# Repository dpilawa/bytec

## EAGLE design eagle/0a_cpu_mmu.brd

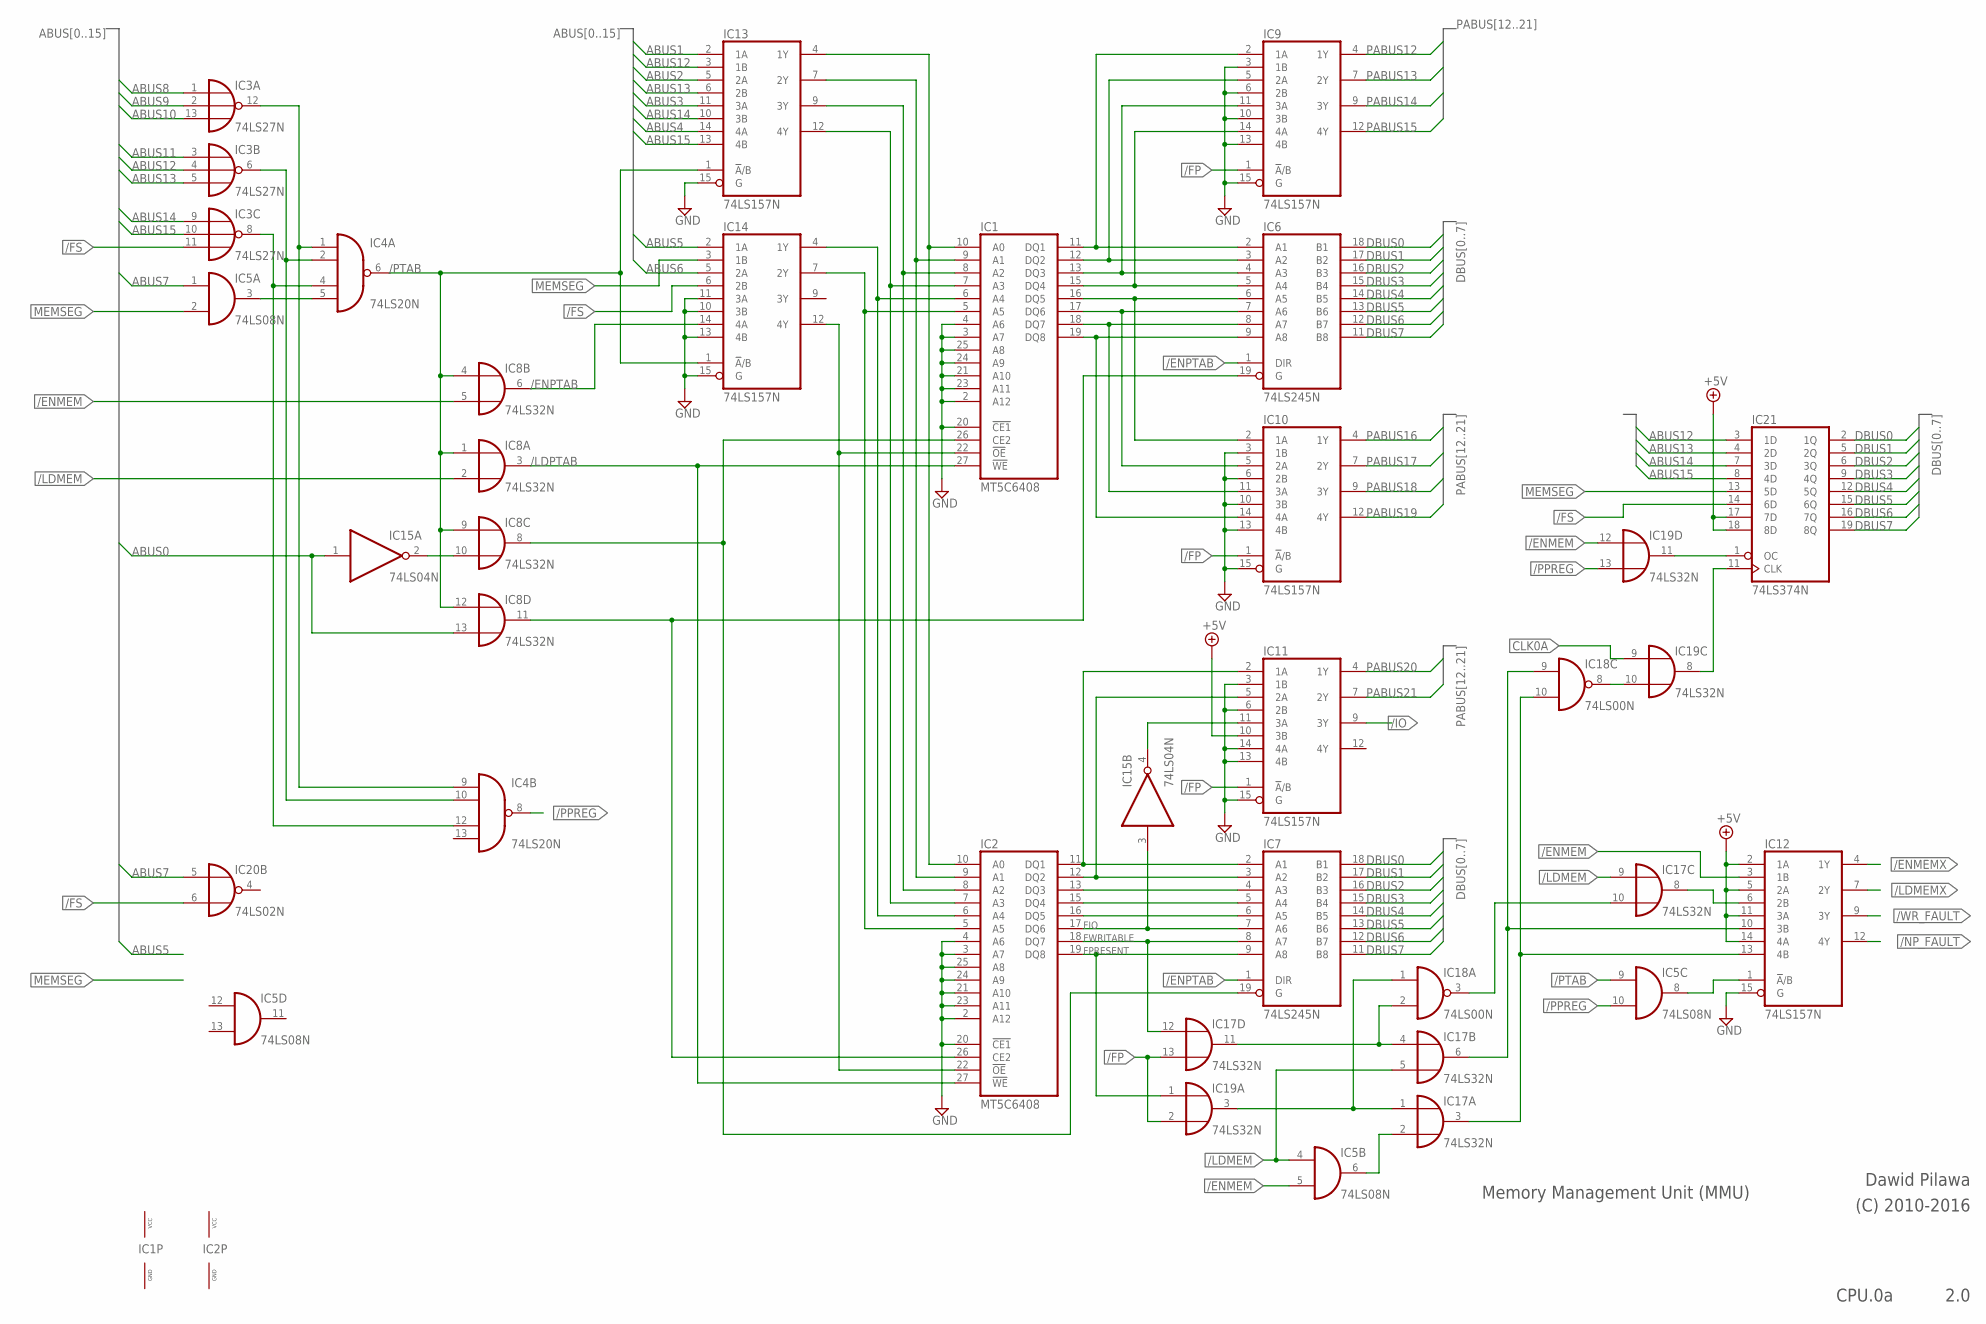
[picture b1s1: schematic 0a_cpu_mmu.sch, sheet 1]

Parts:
IC1, IC2: MT5C6408; DIL28-3
IC3: 74LS27N; DIL14
IC4: 74LS20N; DIL14
IC5: 74LS08N; DIL14
IC6, IC7: 74LS245N; DIL20
IC8, IC17, IC19: 74LS32N; DIL14
IC9, IC10, IC11, IC12, IC13, IC14: 74LS157N; DIL16
IC15: 74LS04N; DIL14
IC18: 74LS00N; DIL14
IC20: 74LS02N; DIL14
IC21: 74LS374N; DIL20

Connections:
+5V: IC11.10 (3B), IC12.2 (1A), IC12.5 (2A), IC12.11 (3A), IC12.14 (4A), IC21.17 (7D), IC21.18 (8D); also elsewhere on the board
/ENMEM: IC5.5 (I1), IC8.5 (I1), IC12.3 (1B), IC19.12 (I0); also elsewhere on the board
/ENMEMX: IC12.4 (1Y)
/ENPTAB: IC6.1 (DIR), IC7.1 (DIR), IC8.6 (O), IC14.14 (4A)
/FP: IC9.1 (!A!/B), IC10.1 (!A!/B), IC11.1 (!A!/B), IC17.13 (I1), IC19.2 (I1); also elsewhere on the board
/FS: IC3.11 (I2), IC14.6 (2B), IC20.6 (I1), IC21.14 (6D); also elsewhere on the board
/IO: IC11.9 (3Y); also elsewhere on the board
/LDMEM: IC5.4 (I0), IC8.2 (I1), IC17.5 (I1), IC17.9 (I0); also elsewhere on the board
/LDMEMX: IC12.7 (2Y)
/LDPTAB: IC1.27 (!WE), IC2.27 (!WE), IC8.3 (O)
/NP_FAULT: IC12.12 (4Y); also elsewhere on the board
/PPREG: IC4.8 (O), IC5.10 (I1), IC19.13 (I1)
/PTAB: IC4.6 (O), IC5.9 (I0), IC8.1 (I0), IC8.4 (I0), IC8.9 (I0), IC8.12 (I0), IC13.1 (!A!/B), IC14.1 (!A!/B)
/WR_FAULT: IC12.9 (3Y); also elsewhere on the board
ABUS0: IC8.13 (I1), IC15.1 (I); also elsewhere on the board
ABUS1: IC13.2 (1A); also elsewhere on the board
ABUS2: IC13.5 (2A); also elsewhere on the board
ABUS3: IC13.11 (3A); also elsewhere on the board
ABUS4: IC13.14 (4A); also elsewhere on the board
ABUS5: IC14.2 (1A); also elsewhere on the board
ABUS6: IC14.5 (2A); also elsewhere on the board
ABUS7: IC5.1 (I0), IC20.5 (I0); also elsewhere on the board
ABUS8: IC3.1 (I0); also elsewhere on the board
ABUS9: IC3.2 (I1); also elsewhere on the board
ABUS10: IC3.13 (I2); also elsewhere on the board
ABUS11: IC3.3 (I0); also elsewhere on the board
ABUS12: IC3.4 (I1), IC13.3 (1B), IC21.3 (1D); also elsewhere on the board
ABUS13: IC3.5 (I2), IC13.6 (2B), IC21.4 (2D); also elsewhere on the board
ABUS14: IC3.9 (I0), IC13.10 (3B), IC21.7 (3D); also elsewhere on the board
ABUS15: IC3.10 (I1), IC13.13 (4B), IC21.8 (4D); also elsewhere on the board
CLK0A: IC19.9 (I0); also elsewhere on the board
DBUS0: IC6.18 (B1), IC7.18 (B1), IC21.2 (1Q); also elsewhere on the board
DBUS1: IC6.17 (B2), IC7.17 (B2), IC21.5 (2Q); also elsewhere on the board
DBUS2: IC6.16 (B3), IC7.16 (B3), IC21.6 (3Q); also elsewhere on the board
DBUS3: IC6.15 (B4), IC7.15 (B4), IC21.9 (4Q); also elsewhere on the board
DBUS4: IC6.14 (B5), IC7.14 (B5), IC21.12 (5Q); also elsewhere on the board
DBUS5: IC6.13 (B6), IC7.13 (B6), IC21.15 (6Q); also elsewhere on the board
DBUS6: IC6.12 (B7), IC7.12 (B7), IC21.16 (7Q); also elsewhere on the board
DBUS7: IC6.11 (B8), IC7.11 (B8), IC21.19 (8Q); also elsewhere on the board
FIO: IC2.17 (DQ6), IC7.7 (A6), IC15.3 (I)
FPRESENT: IC2.19 (DQ8), IC7.9 (A8), IC19.1 (I0)
FWRITABLE: IC2.18 (DQ7), IC7.8 (A7), IC17.12 (I0)
GND: IC1.2 (A12), IC1.3 (A7), IC1.4 (A6), IC1.14 (GND), IC1.20 (!CE1), IC1.21 (A10), IC1.23 (A11), IC1.24 (A9), IC1.25 (A8), IC2.2 (A12), IC2.3 (A7), IC2.4 (A6), IC2.14 (GND), IC2.20 (!CE1), IC2.21 (A10), IC2.23 (A11), IC2.24 (A9), IC2.25 (A8), IC3.7 (GND), IC4.7 (GND), IC5.7 (GND), IC6.10 (GND), IC7.10 (GND), IC8.7 (GND), IC9.3 (1B), IC9.6 (2B), IC9.8 (GND), IC9.10 (3B), IC9.13 (4B), IC9.15 (G), IC10.3 (1B), IC10.6 (2B), IC10.8 (GND), IC10.10 (3B), IC10.13 (4B), IC10.15 (G), IC11.3 (1B), IC11.6 (2B), IC11.8 (GND), IC11.13 (4B), IC11.14 (4A), IC11.15 (G), IC12.8 (GND), IC12.15 (G), IC13.8 (GND), IC13.15 (G), IC14.8 (GND), IC14.10 (3B), IC14.11 (3A), IC14.13 (4B), IC14.15 (G), IC15.7 (GND), IC17.7 (GND), IC18.7 (GND), IC19.7 (GND), IC20.7 (GND), IC21.10 (GND); also elsewhere on the board
MEMSEG: IC5.2 (I1), IC14.3 (1B), IC21.13 (5D); also elsewhere on the board
unnamed: IC3.12 (O), IC4.1 (I0), IC4.9 (I0)
unnamed: IC3.6 (O), IC4.2 (I1), IC4.10 (I1)
unnamed: IC4.5 (I3), IC5.3 (O)
unnamed: IC1.11 (DQ1), IC6.2 (A1), IC9.2 (1A)
unnamed: IC1.12 (DQ2), IC6.3 (A2), IC9.5 (2A)
unnamed: IC1.13 (DQ3), IC6.4 (A3), IC9.11 (3A)
unnamed: IC1.15 (DQ4), IC6.5 (A4), IC9.14 (4A)
unnamed: IC1.16 (DQ5), IC6.6 (A5), IC10.2 (1A)
unnamed: IC1.17 (DQ6), IC6.7 (A6), IC10.5 (2A)
unnamed: IC1.18 (DQ7), IC6.8 (A7), IC10.11 (3A)
unnamed: IC1.19 (DQ8), IC6.9 (A8), IC10.14 (4A)
unnamed: IC2.11 (DQ1), IC7.2 (A1), IC11.2 (1A)
unnamed: IC2.12 (DQ2), IC7.3 (A2), IC11.5 (2A)
unnamed: IC2.13 (DQ3), IC7.4 (A3)
unnamed: IC2.15 (DQ4), IC7.5 (A4)
unnamed: IC2.16 (DQ5), IC7.6 (A5)
unnamed: IC11.11 (3A), IC15.4 (O)
unnamed: IC5.6 (O), IC17.2 (I1)
unnamed: IC12.6 (2B), IC17.8 (O)
unnamed: IC1.10 (A0), IC2.10 (A0), IC13.4 (1Y)
unnamed: IC1.9 (A1), IC2.9 (A1), IC13.7 (2Y)
unnamed: IC1.8 (A2), IC2.8 (A2), IC13.9 (3Y)
unnamed: IC1.7 (A3), IC2.7 (A3), IC13.12 (4Y)
unnamed: IC1.6 (A4), IC2.6 (A4), IC14.4 (1Y)
unnamed: IC1.5 (A5), IC2.5 (A5), IC14.7 (2Y)
unnamed: IC1.26 (CE2), IC7.19 (G), IC8.8 (O)
unnamed: IC2.26 (CE2), IC6.19 (G), IC8.11 (O)
unnamed: IC1.22 (!OE), IC2.22 (!OE), IC14.12 (4Y)
unnamed: IC8.10 (I1), IC15.2 (O)
unnamed: IC12.10 (3B), IC17.6 (O), IC18.9 (I0)
unnamed: IC12.13 (4B), IC17.3 (O), IC18.10 (I1)
unnamed: IC17.10 (I1), IC18.3 (O)
unnamed: IC17.4 (I0), IC17.11 (O), IC18.2 (I1)
unnamed: IC17.1 (I0), IC18.1 (I0), IC19.3 (O)
unnamed: IC3.8 (O), IC4.4 (I2), IC4.12 (I2)
unnamed: IC5.8 (O), IC12.1 (!A!/B)
unnamed: IC18.8 (O), IC19.10 (I1)
unnamed: IC19.8 (O), IC21.11 (CLK)
unnamed: IC19.11 (O), IC21.1 (OC)
PABUS12: IC9.4 (1Y); also elsewhere on the board
PABUS13: IC9.7 (2Y); also elsewhere on the board
PABUS14: IC9.9 (3Y); also elsewhere on the board
PABUS15: IC9.12 (4Y); also elsewhere on the board
PABUS16: IC10.4 (1Y); also elsewhere on the board
PABUS17: IC10.7 (2Y); also elsewhere on the board
PABUS18: IC10.9 (3Y); also elsewhere on the board
PABUS19: IC10.12 (4Y); also elsewhere on the board
PABUS20: IC11.4 (1Y); also elsewhere on the board
PABUS21: IC11.7 (2Y); also elsewhere on the board
VCC: IC1.28 (VCC), IC2.28 (VCC), IC3.14 (VCC), IC4.14 (VCC), IC5.14 (VCC), IC6.20 (VCC), IC7.20 (VCC), IC8.14 (VCC), IC9.16 (VCC), IC10.16 (VCC), IC11.16 (VCC), IC12.16 (VCC), IC13.16 (VCC), IC14.16 (VCC), IC15.14 (VCC), IC17.14 (VCC), IC18.14 (VCC), IC19.14 (VCC), IC20.14 (VCC), IC21.20 (VCC)

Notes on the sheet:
Memory Management Unit (MMU)
Dawid Pilawa
(C) 2010-2016
CPU.0a
2.0

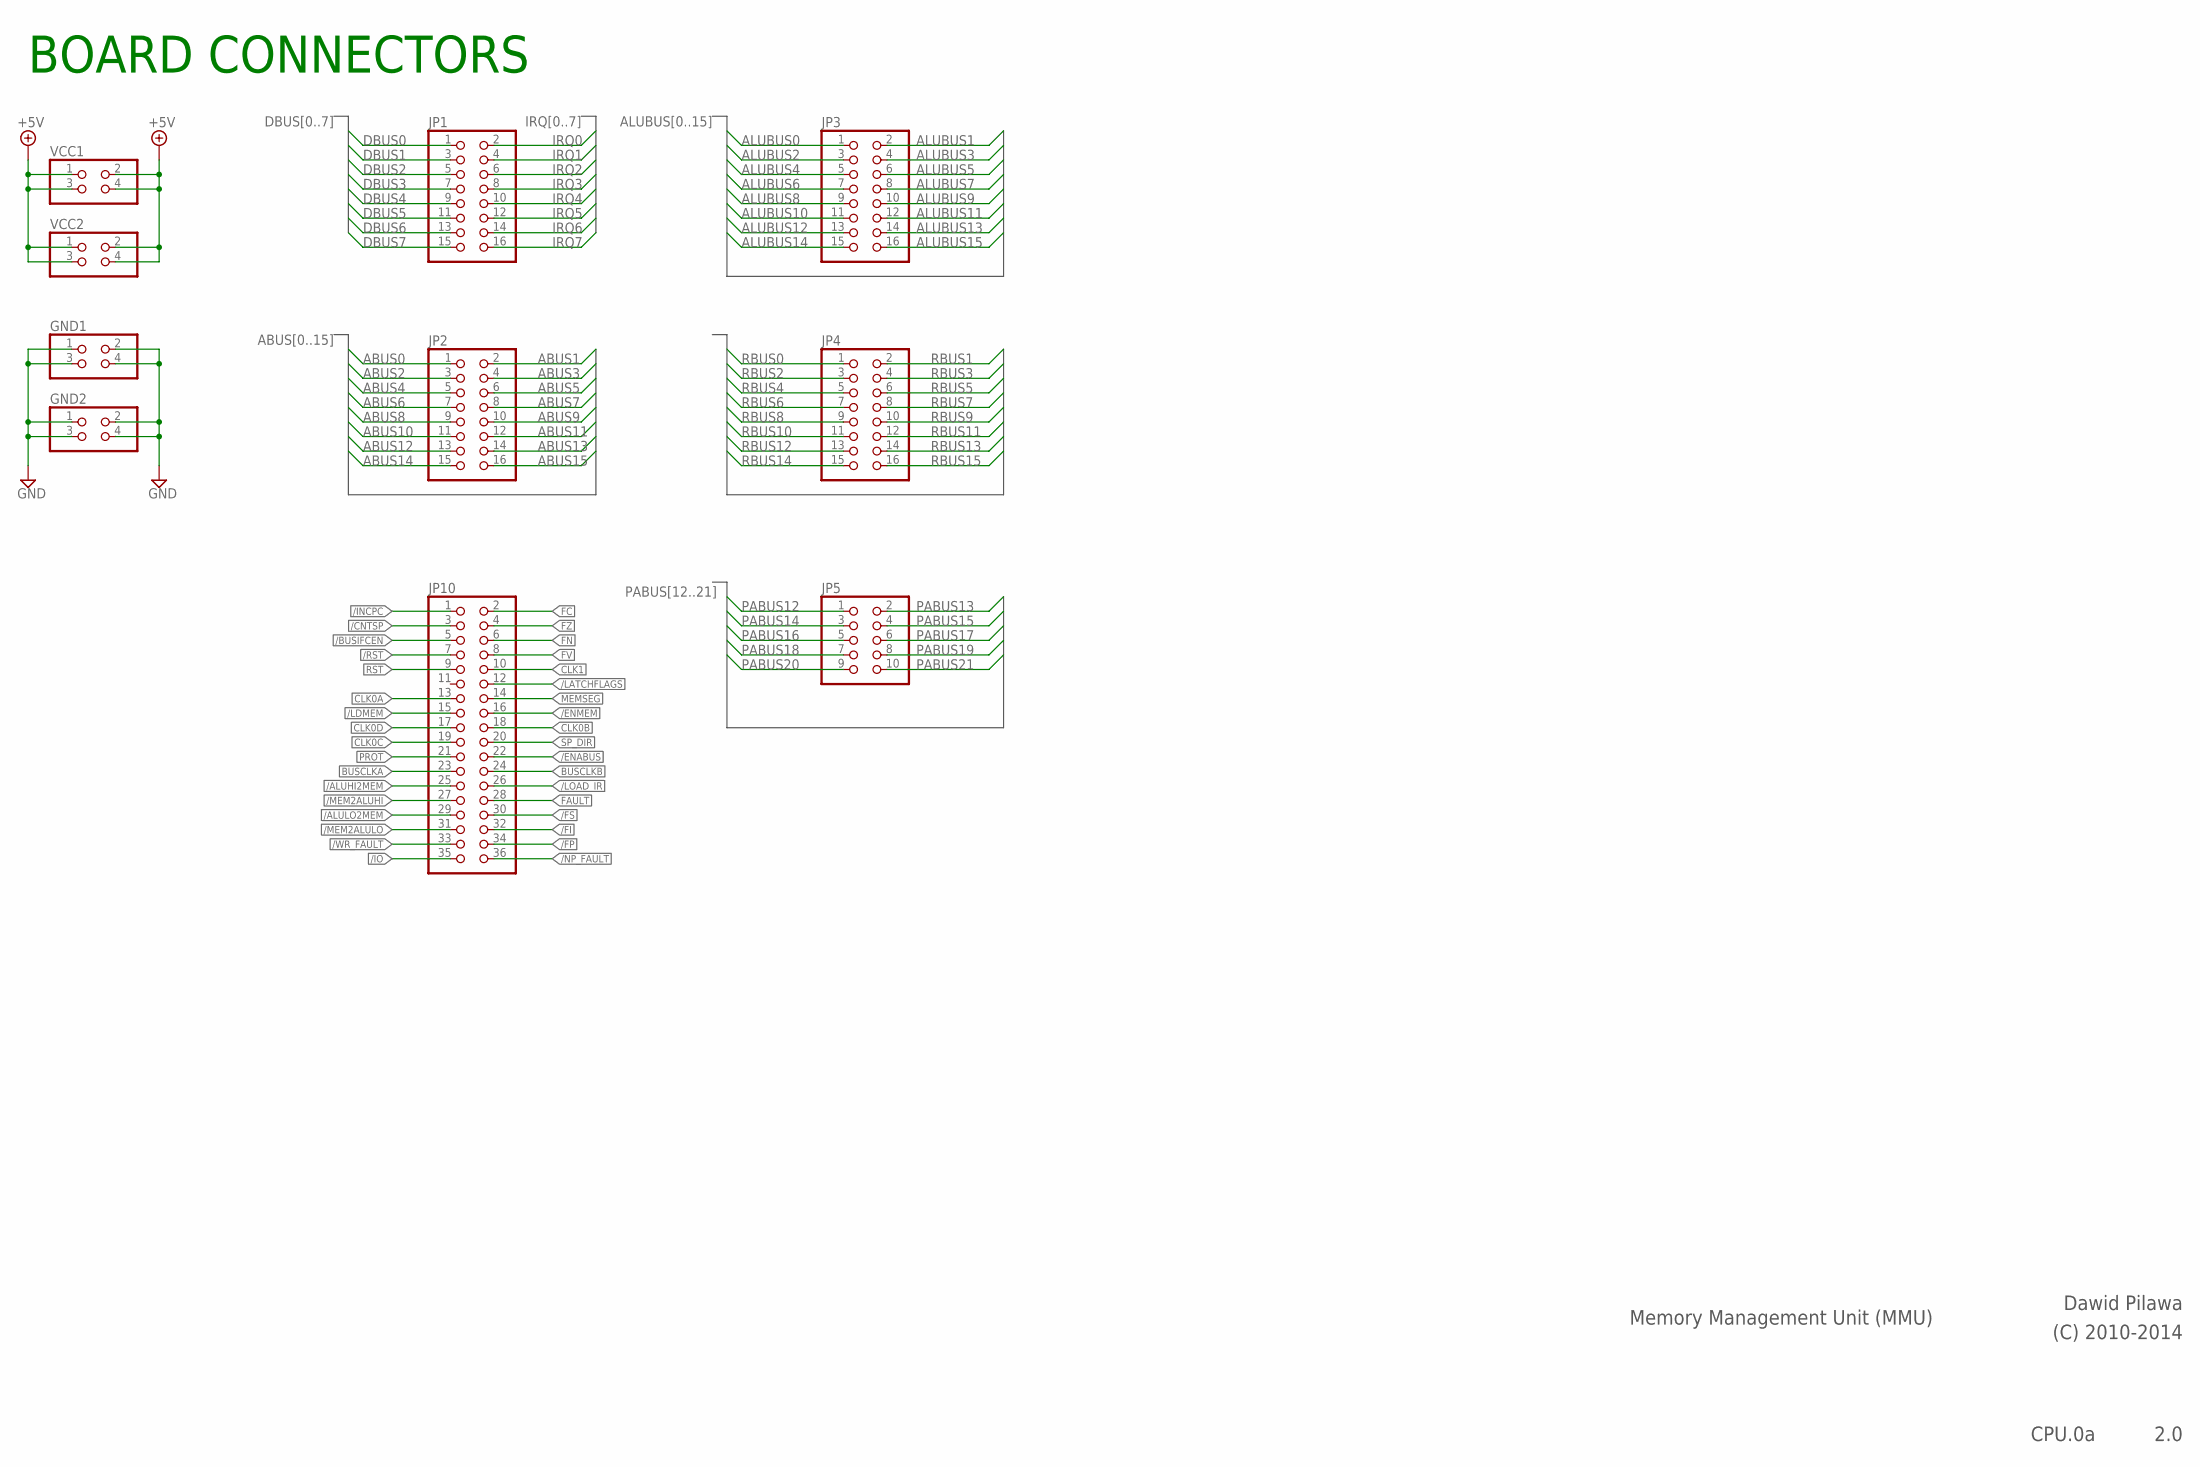
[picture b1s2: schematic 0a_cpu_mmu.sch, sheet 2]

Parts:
GND1, GND2: PINHD-2X2; 2X02
JP1, JP2, JP3, JP4: PINHD-2X8; 2X08
JP5: PINHD-2X5; 2X05
JP10: PINHD-2X18; 2X18
VCC1, VCC2: PINHD-2X2; 2X02

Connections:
+5V: VCC1.1, VCC1.2, VCC1.3, VCC1.4, VCC2.1, VCC2.2, VCC2.3, VCC2.4; also elsewhere on the board
/ALUHI2MEM: JP10.25
/ALULO2MEM: JP10.29
/BUSIFCEN: JP10.5
/CNTSP: JP10.3
/ENABUS: JP10.22
/ENMEM: JP10.16; also elsewhere on the board
/FI: JP10.32
/FP: JP10.34; also elsewhere on the board
/FS: JP10.30; also elsewhere on the board
/INCPC: JP10.1
/IO: JP10.35; also elsewhere on the board
/LATCHFLAGS: JP10.12
/LDMEM: JP10.15; also elsewhere on the board
/LOAD_IR: JP10.26
/MEM2ALUHI: JP10.27
/MEM2ALULO: JP10.31
/NP_FAULT: JP10.36; also elsewhere on the board
/RST: JP10.7
/WR_FAULT: JP10.33; also elsewhere on the board
ABUS0: JP2.1; also elsewhere on the board
ABUS1: JP2.2; also elsewhere on the board
ABUS2: JP2.3; also elsewhere on the board
ABUS3: JP2.4; also elsewhere on the board
ABUS4: JP2.5; also elsewhere on the board
ABUS5: JP2.6; also elsewhere on the board
ABUS6: JP2.7; also elsewhere on the board
ABUS7: JP2.8; also elsewhere on the board
ABUS8: JP2.9; also elsewhere on the board
ABUS9: JP2.10; also elsewhere on the board
ABUS10: JP2.11; also elsewhere on the board
ABUS11: JP2.12; also elsewhere on the board
ABUS12: JP2.13; also elsewhere on the board
ABUS13: JP2.14; also elsewhere on the board
ABUS14: JP2.15; also elsewhere on the board
ABUS15: JP2.16; also elsewhere on the board
ALUBUS0: JP3.1
ALUBUS1: JP3.2
ALUBUS2: JP3.3
ALUBUS3: JP3.4
ALUBUS4: JP3.5
ALUBUS5: JP3.6
ALUBUS6: JP3.7
ALUBUS7: JP3.8
ALUBUS8: JP3.9
ALUBUS9: JP3.10
ALUBUS10: JP3.11
ALUBUS11: JP3.12
ALUBUS12: JP3.13
ALUBUS13: JP3.14
ALUBUS14: JP3.15
ALUBUS15: JP3.16
BUSCLKA: JP10.23
BUSCLKB: JP10.24
CLK0A: JP10.13; also elsewhere on the board
CLK0B: JP10.18
CLK0C: JP10.19
CLK0D: JP10.17
CLK1: JP10.10
DBUS0: JP1.1; also elsewhere on the board
DBUS1: JP1.3; also elsewhere on the board
DBUS2: JP1.5; also elsewhere on the board
DBUS3: JP1.7; also elsewhere on the board
DBUS4: JP1.9; also elsewhere on the board
DBUS5: JP1.11; also elsewhere on the board
DBUS6: JP1.13; also elsewhere on the board
DBUS7: JP1.15; also elsewhere on the board
FAULT: JP10.28
FC: JP10.2
FN: JP10.6
FV: JP10.8
FZ: JP10.4
GND: GND1.1, GND1.2, GND1.3, GND1.4, GND2.1, GND2.2, GND2.3, GND2.4; also elsewhere on the board
IRQ0: JP1.2
IRQ1: JP1.4
IRQ2: JP1.6
IRQ3: JP1.8
IRQ4: JP1.10
IRQ5: JP1.12
IRQ6: JP1.14
IRQ7: JP1.16
MEMSEG: JP10.14; also elsewhere on the board
PABUS12: JP5.1; also elsewhere on the board
PABUS13: JP5.2; also elsewhere on the board
PABUS14: JP5.3; also elsewhere on the board
PABUS15: JP5.4; also elsewhere on the board
PABUS16: JP5.5; also elsewhere on the board
PABUS17: JP5.6; also elsewhere on the board
PABUS18: JP5.7; also elsewhere on the board
PABUS19: JP5.8; also elsewhere on the board
PABUS20: JP5.9; also elsewhere on the board
PABUS21: JP5.10; also elsewhere on the board
PROT: JP10.21
RBUS0: JP4.1
RBUS1: JP4.2
RBUS2: JP4.3
RBUS3: JP4.4
RBUS4: JP4.5
RBUS5: JP4.6
RBUS6: JP4.7
RBUS7: JP4.8
RBUS8: JP4.9
RBUS9: JP4.10
RBUS10: JP4.11
RBUS11: JP4.12
RBUS12: JP4.13
RBUS13: JP4.14
RBUS14: JP4.15
RBUS15: JP4.16
RST: JP10.9
SP_DIR: JP10.20

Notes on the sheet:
Memory Management Unit (MMU)
Dawid Pilawa
(C) 2010-2014
CPU.0a
2.0
BOARD CONNECTORS

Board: 2 copper layers, 30 parts (0 on the bottom side), 92 nets, no tracks yet.

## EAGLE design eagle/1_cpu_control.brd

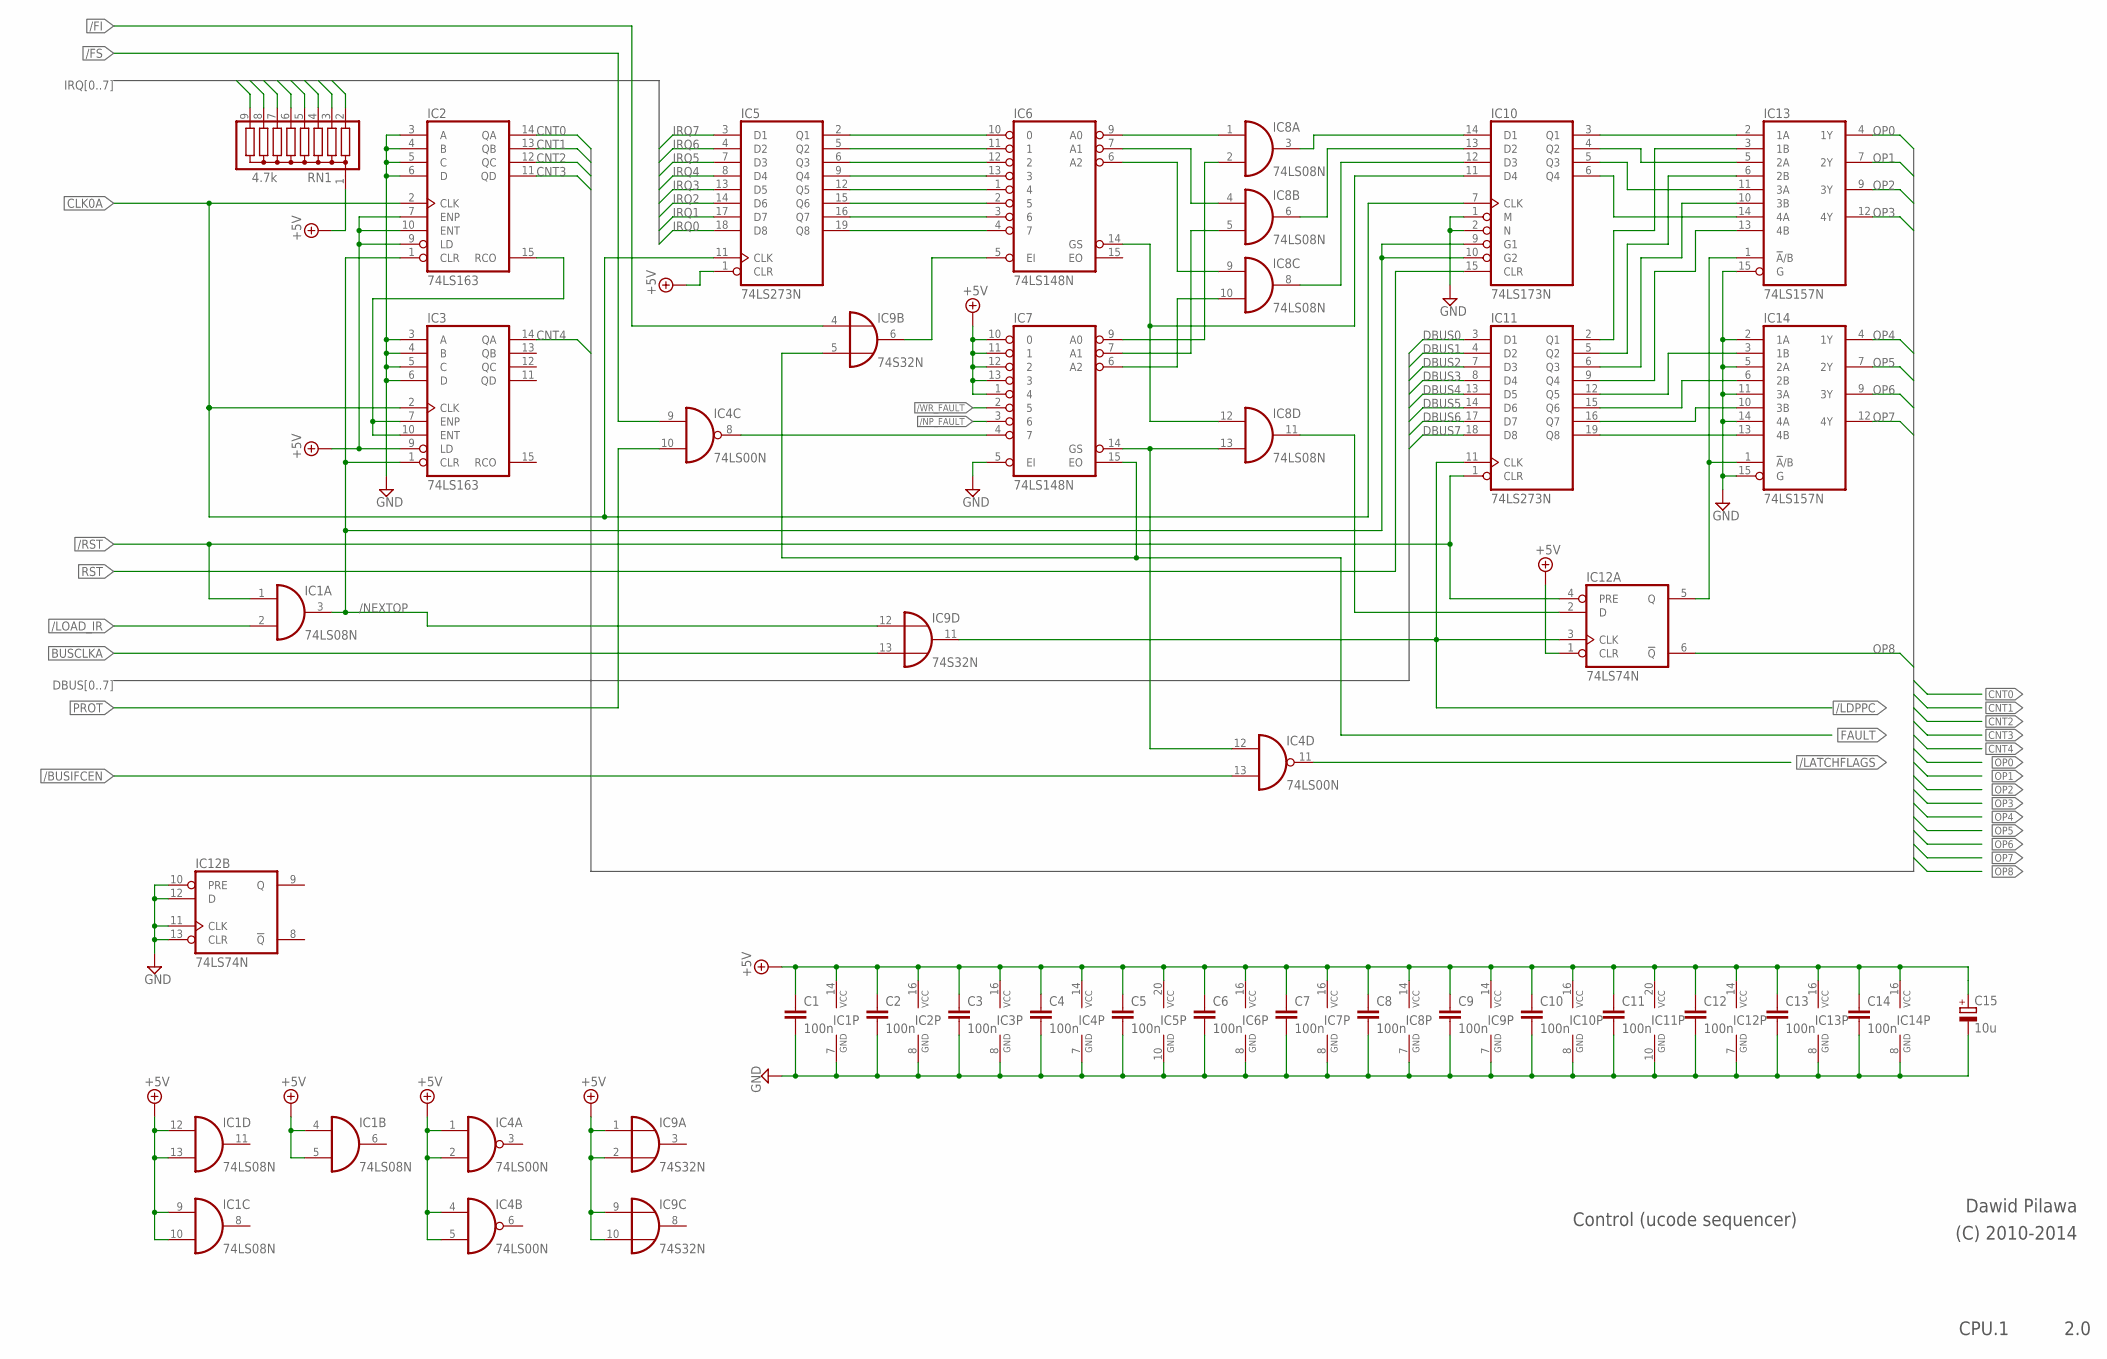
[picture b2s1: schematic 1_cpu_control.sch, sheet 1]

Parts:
C1, C2, C3, C4, C5, C6, C7, C8, C9, C10, C11, C12, C13, C14: 100n; C050-024X044
C15: 10u; E5-6
IC1, IC8: 74LS08N; DIL14
IC2, IC3: 74LS163; DIL16
IC4: 74LS00N; DIL14
IC5, IC11: 74LS273N; DIL20
IC6, IC7: 74LS148N; DIL16
IC9: 74S32N; DIL14
IC10: 74LS173N; DIL16
IC12: 74LS74N; DIL14
IC13, IC14: 74LS157N; DIL16
RN1: 4.7k; SIL9

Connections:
+5V: C1.1, C2.1, C3.1, C4.1, C5.1, C6.1, C7.1, C8.1, C9.1, C10.1, C11.1, C12.1, C13.1, C14.1, C15.+, IC1.4 (I0), IC1.5 (I1), IC1.9 (I0), IC1.10 (I1), IC1.12 (I0), IC1.13 (I1), IC1.14 (VCC), IC2.7 (ENP), IC2.9 (LD), IC2.10 (ENT), IC2.16 (VCC), IC3.9 (LD), IC3.16 (VCC), IC4.1 (I0), IC4.2 (I1), IC4.4 (I0), IC4.5 (I1), IC4.14 (VCC), IC5.1 (CLR), IC5.20 (VCC), IC6.16 (VCC), IC7.1 (4), IC7.10 (0), IC7.11 (1), IC7.12 (2), IC7.13 (3), IC7.16 (VCC), IC8.14 (VCC), IC9.1 (I0), IC9.2 (I1), IC9.9 (I0), IC9.10 (I1), IC9.14 (VCC), IC10.16 (VCC), IC11.20 (VCC), IC12.1 (CLR), IC12.14 (VCC), IC13.16 (VCC), IC14.16 (VCC), RN1.1; also elsewhere on the board
/BUSIFCEN: IC4.13 (I1); also elsewhere on the board
/FAULT_PF: IC4.8 (O), IC7.4 (7)
/FI: IC9.4 (I0); also elsewhere on the board
/FS: IC4.9 (I0); also elsewhere on the board
/LATCHFLAGS: IC4.11 (O); also elsewhere on the board
/LDPPC: IC9.11 (O), IC11.11 (CLK), IC12.3 (CLK); also elsewhere on the board
/LOAD_IR: IC1.2 (I1); also elsewhere on the board
/NEXTOP: IC1.3 (O), IC2.1 (CLR), IC3.1 (CLR), IC9.12 (I0), IC10.9 (G1), IC10.10 (G2)
/NP_FAULT: IC7.3 (6); also elsewhere on the board
/RST: IC1.1 (I0), IC11.1 (CLR), IC12.4 (PRE); also elsewhere on the board
/WR_FAULT: IC7.2 (5); also elsewhere on the board
BUSCLKA: IC9.13 (I1); also elsewhere on the board
CLK0A: IC2.2 (CLK), IC3.2 (CLK), IC5.11 (CLK), IC10.7 (CLK); also elsewhere on the board
CNT0: IC2.14 (QA); also elsewhere on the board
CNT1: IC2.13 (QB); also elsewhere on the board
CNT2: IC2.12 (QC); also elsewhere on the board
CNT3: IC2.11 (QD); also elsewhere on the board
CNT4: IC3.14 (QA); also elsewhere on the board
DBUS0: IC11.3 (D1); also elsewhere on the board
DBUS1: IC11.4 (D2); also elsewhere on the board
DBUS2: IC11.7 (D3); also elsewhere on the board
DBUS3: IC11.8 (D4); also elsewhere on the board
DBUS4: IC11.13 (D5); also elsewhere on the board
DBUS5: IC11.14 (D6); also elsewhere on the board
DBUS6: IC11.17 (D7); also elsewhere on the board
DBUS7: IC11.18 (D8); also elsewhere on the board
FAULT: IC7.15 (EO), IC9.5 (I1); also elsewhere on the board
GND: C1.2, C2.2, C3.2, C4.2, C5.2, C6.2, C7.2, C8.2, C9.2, C10.2, C11.2, C12.2, C13.2, C14.2, C15.-, IC1.7 (GND), IC2.3 (A), IC2.4 (B), IC2.5 (C), IC2.6 (D), IC2.8 (GND), IC3.3 (A), IC3.4 (B), IC3.5 (C), IC3.6 (D), IC3.8 (GND), IC4.7 (GND), IC5.10 (GND), IC6.8 (GND), IC7.5 (EI), IC7.8 (GND), IC8.7 (GND), IC9.7 (GND), IC10.1 (M), IC10.2 (N), IC10.8 (GND), IC11.10 (GND), IC12.7 (GND), IC12.10 (PRE), IC12.11 (CLK), IC12.12 (D), IC12.13 (CLR), IC13.8 (GND), IC13.15 (G), IC14.2 (1A), IC14.5 (2A), IC14.8 (GND), IC14.11 (3A), IC14.14 (4A), IC14.15 (G); also elsewhere on the board
IRQ0: IC5.18 (D8), RN1.9; also elsewhere on the board
IRQ1: IC5.17 (D7), RN1.8; also elsewhere on the board
IRQ2: IC5.14 (D6), RN1.7; also elsewhere on the board
IRQ3: IC5.13 (D5), RN1.6; also elsewhere on the board
IRQ4: IC5.8 (D4), RN1.5; also elsewhere on the board
IRQ5: IC5.7 (D3), RN1.4; also elsewhere on the board
IRQ6: IC5.4 (D2), RN1.3; also elsewhere on the board
IRQ7: IC5.3 (D1), RN1.2; also elsewhere on the board
unnamed: IC6.9 (A0), IC8.1 (I0)
unnamed: IC2.15 (RCO), IC3.7 (ENP), IC3.10 (ENT)
unnamed: IC7.9 (A0), IC8.2 (I1)
unnamed: IC6.7 (A1), IC8.4 (I0)
unnamed: IC7.7 (A1), IC8.5 (I1)
unnamed: IC7.6 (A2), IC8.10 (I1)
unnamed: IC6.6 (A2), IC8.9 (I0)
unnamed: IC6.14 (GS), IC8.12 (I0), IC10.11 (D4)
unnamed: IC4.12 (I0), IC7.14 (GS), IC8.13 (I1)
unnamed: IC8.3 (O), IC10.14 (D1)
unnamed: IC8.6 (O), IC10.13 (D2)
unnamed: IC8.8 (O), IC10.12 (D3)
unnamed: IC8.11 (O), IC12.2 (D)
unnamed: IC11.5 (Q2), IC13.6 (2B)
unnamed: IC10.3 (Q1), IC13.2 (1A)
unnamed: IC10.4 (Q2), IC13.5 (2A)
unnamed: IC10.5 (Q3), IC13.11 (3A)
unnamed: IC10.6 (Q4), IC13.14 (4A)
unnamed: IC11.19 (Q8), IC14.13 (4B)
unnamed: IC11.16 (Q7), IC14.10 (3B)
unnamed: IC11.15 (Q6), IC14.6 (2B)
unnamed: IC11.12 (Q5), IC14.3 (1B)
unnamed: IC11.2 (Q1), IC13.3 (1B)
unnamed: IC6.5 (EI), IC9.6 (O)
unnamed: IC11.6 (Q3), IC13.10 (3B)
unnamed: IC11.9 (Q4), IC13.13 (4B)
unnamed: IC12.5 (Q), IC13.1 (!A!/B), IC14.1 (!A!/B)
unnamed: IC5.19 (Q8), IC6.4 (7)
unnamed: IC5.16 (Q7), IC6.3 (6)
unnamed: IC5.15 (Q6), IC6.2 (5)
unnamed: IC5.12 (Q5), IC6.1 (4)
unnamed: IC5.9 (Q4), IC6.13 (3)
unnamed: IC5.6 (Q3), IC6.12 (2)
unnamed: IC5.5 (Q2), IC6.11 (1)
unnamed: IC5.2 (Q1), IC6.10 (0)
OP0: IC13.4 (1Y); also elsewhere on the board
OP1: IC13.7 (2Y); also elsewhere on the board
OP2: IC13.9 (3Y); also elsewhere on the board
OP3: IC13.12 (4Y); also elsewhere on the board
OP4: IC14.4 (1Y); also elsewhere on the board
OP5: IC14.7 (2Y); also elsewhere on the board
OP6: IC14.9 (3Y); also elsewhere on the board
OP7: IC14.12 (4Y); also elsewhere on the board
OP8: IC12.6 (!Q); also elsewhere on the board
PROT: IC4.10 (I1); also elsewhere on the board
RST: IC10.15 (CLR); also elsewhere on the board

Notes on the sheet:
Control (ucode sequencer)
2.0
Dawid Pilawa
(C) 2010-2014
CPU.1
